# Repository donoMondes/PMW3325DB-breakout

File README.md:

# PMW3325DB-TWV1 breakout board

This repository contains PCB design files for a breakout board for the PMW3325DB optical mouse sensor.

The board doesn't do any level shifting so it only works with 3.3V logic.

The dimensions of the board are 45x25mm and the mounting holes are for M2 screws with meta inserts.

The files in the [fabrication](fabrication) folder can be used to order this board from JLCPCB with SMT assembly. The board you get includes everything except the actual sensor. If some of the specific components are out of stock, try to find an equivalent with the same package and parameters.

If the volatage regulator **TCR2EF19** is out of stock, you can replace it by using the following configuration :

| **Reference** | **Part Name**         | **JLCPCB P/N**    |**Description**|
|------------   |---                    |---                |---|
| U2            | TLV74318PDBVR         | C15849            | Voltage regulator with Vout = 1.8v  |
| C1            | C15849 CL10A105KB8NNNC| C485152           | Capacitor of 1uF  |

**Warning** Don't forget to turn the TLV74318PDBVR when making the position during the PCBA process

The sensor chip should be soldered on the top side (the side where all the other components are). The dot marks pin 1. The optic goes on the bottom side.

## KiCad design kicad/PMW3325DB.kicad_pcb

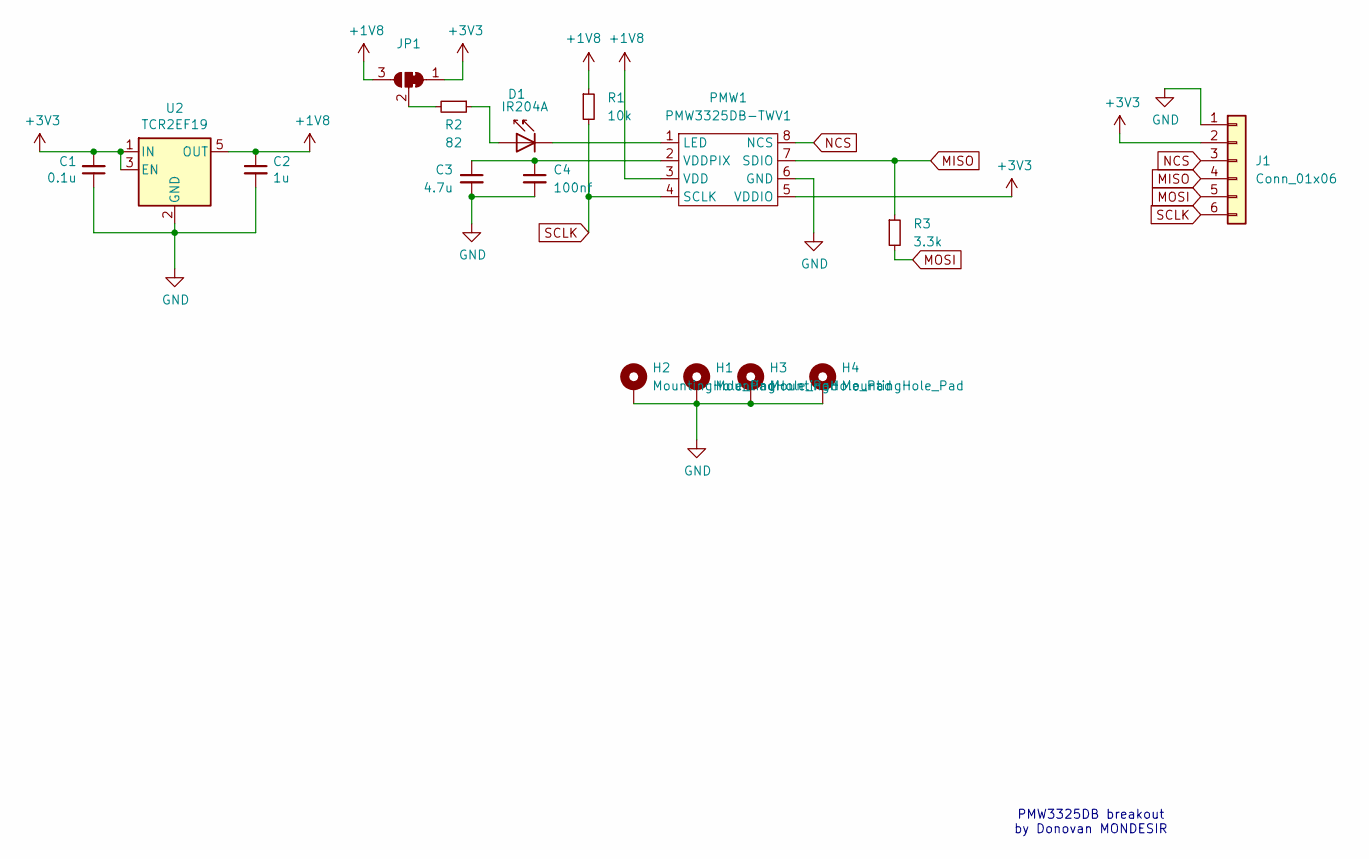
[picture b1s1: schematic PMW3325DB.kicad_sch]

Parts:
C1: 0.1u; C_0603_1608Metric; LCSC C14663
C2: 1u; C_0603_1608Metric; LCSC C15849
C3: 4.7u; C_0603_1608Metric; LCSC C19666
C4: 100nf; C_0603_1608Metric; LCSC C19666
D1: IR204A; LED_D5.0mm_Horizontal_O1.27mm_Z15.0mm
H1, H2, H3, H4: MountingHole_Pad; MountingHole_2.2mm_M2_Pad
J1: Conn_01x06; PinHeader_1x06_P2.54mm_Vertical
JP1: SolderJumper-3_P1.3mm_Bridged12_RoundedPad1.0x1.5mm
PMW1: PMW3325DB-TWV1
R1: 10k; R_0603_1608Metric; LCSC C25804
R2: 82; R_0603_1608Metric; LCSC C25804
R3: 3.3k; R_0603_1608Metric; LCSC C25804
U2: TCR2EF19; SOT-23-5; LCSC C146366

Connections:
+1V8: C2.1, JP1.3 (B), PMW1.3 (VDD), R1.1, U2.5 (OUT)
+3V3: C1.2, J1.2, JP1.1 (A), PMW1.5 (VDDIO), U2.1 (IN), U2.3 (EN)
GND: C1.1, C2.2, C3.2, C4.2, H1.1, H2.1, H3.1, H4.1, J1.1, PMW1.6 (GND), U2.2 (GND)
MISO: J1.4, PMW1.7 (SDIO), R3.1
MOSI: J1.5, R3.2
NCS: J1.3, PMW1.8 (NCS)
unnamed: D1.2 (A), R2.1
unnamed: D1.1 (K), PMW1.1 (LED)
unnamed: JP1.2 (C), R2.2
unnamed: C3.1, C4.1, PMW1.2 (VDDPIX)
SCLK: J1.6, PMW1.4 (SCLK), R1.2

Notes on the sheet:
PMW3325DB breakout by Donovan MONDESIR

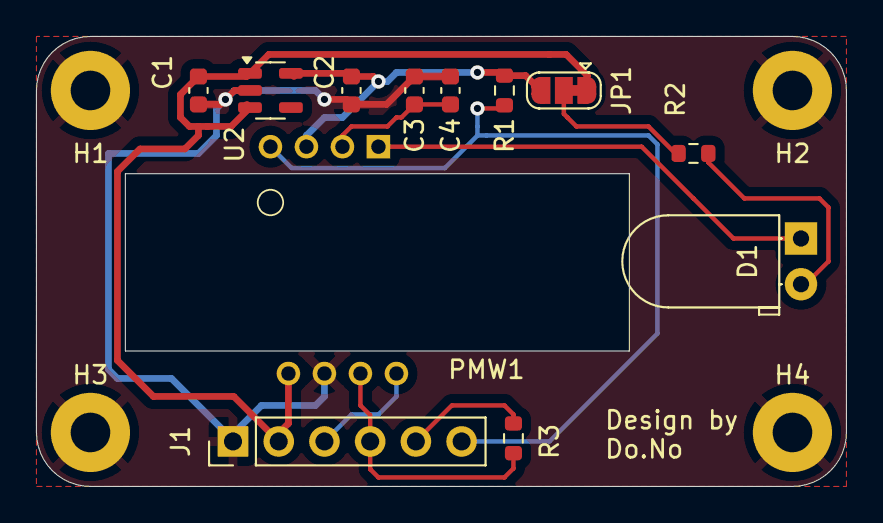
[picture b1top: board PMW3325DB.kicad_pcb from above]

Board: 2 copper layers, 45.0 x 25.0 mm, 16 parts (0 on the bottom side), 11 nets.

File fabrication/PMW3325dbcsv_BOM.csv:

"Reference","Value","Datasheet","Footprint","Qty","DNP"
"C1","0.1u","~","Capacitor_SMD:C_0603_1608Metric","1",""
"C2","1u","~","Capacitor_SMD:C_0603_1608Metric","1",""
"C3","4.7u","~","Capacitor_SMD:C_0603_1608Metric","1",""
"C4","100nf","~","Capacitor_SMD:C_0603_1608Metric","1",""
"D1","IR204A","http://www.everlight.com/file/ProductFile/IR204-A.pdf","LED_THT:LED_D5.0mm_Horizontal_O1.27mm_Z15.0mm","1",""
"J1","Conn_01x06","~","Connector _PINHeader:PinHeader_1x06_P2.54mm_Vertical","1",""
"PMW1","PMW3325DB-TWV1","","adns 5050:PMW3325DB-TWV1","1",""
"R1","10k","~","Resistor_SMD:R_0603_1608Metric","1",""
"R2","82","~","Resistor_SMD:R_0603_1608Metric","1",""
"R3","3.3k","~","Resistor_SMD:R_0603_1608Metric","1",""
"U2","TCR2EF19","","Package_TO_SOT_SMD:SOT-23-5","1",""

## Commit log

2024-09-21 [fabrication] File needed for the fabrication process
2024-09-21 [kicad] kicad file for the pcb project
2024-09-21 [images] render of the pcb
2024-09-21 [README] Updated version
